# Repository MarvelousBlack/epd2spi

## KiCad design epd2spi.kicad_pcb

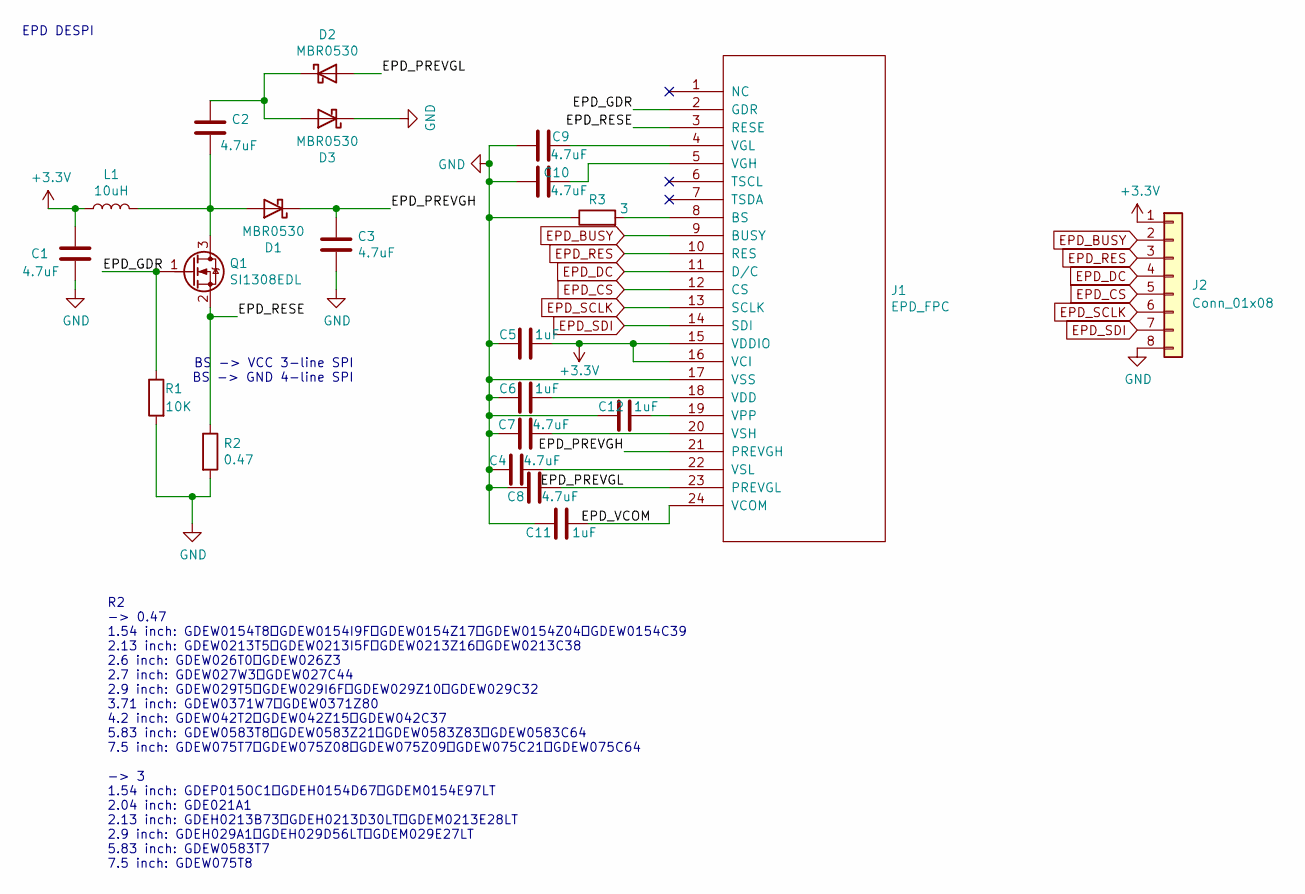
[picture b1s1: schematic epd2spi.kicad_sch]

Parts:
C1, C2, C3, C4, C7, C8, C9, C10: 4.7uF; C_0603_1608Metric
C5, C6, C11, C12: 1uF; C_0603_1608Metric
D1, D2, D3: MBR0530; D_SOD-123
J1: EPD_FPC; FPC-SMD_24P-L17.5-W5.4-P0.50; LCSC C11092
J2: Conn_01x08; PinHeader_1x08_P2.54mm_Vertical
L1: 10uH; L_Taiyo-Yuden_MD-4040
Q1: SI1308EDL; SOT-323_SC-70
R1: 10K; R_0603_1608Metric
R2: 0.47; R_0805_2012Metric
R3: 3; R_0805_2012Metric

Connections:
+3V3: C1.1, C5.1, J1.15 (VDDIO), J1.16 (VCI), J2.1, L1.1
/EPD_GDR: J1.2 (GDR), Q1.1 (G), R1.1
/EPD_PREVGH: C3.1, D1.1 (K), J1.21 (PREVGH)
/EPD_PREVGL: C8.2, D2.2 (A), J1.23 (PREVGL)
/EPD_RESE: J1.3 (RESE), Q1.2 (S), R2.1
/EPD_VCOM: C11.2, J1.24 (VCOM)
EPD_BUSY: J1.9 (BUSY), J2.2
EPD_CS: J1.12 (CS), J2.5
EPD_DC: J1.11 (D/C), J2.4
EPD_RES: J1.10 (RES), J2.3
EPD_SCLK: J1.13 (SCLK), J2.6
EPD_SDI: J1.14 (SDI), J2.7
GND: C1.2, C3.2, C4.1, C5.2, C6.2, C7.1, C8.1, C9.1, C10.1, C11.1, C12.2, D3.1 (K), J1.17 (VSS), J2.8, R1.2, R2.2, R3.1
unnamed: C2.1, D2.1 (K), D3.2 (A)
unnamed: C2.2, D1.2 (A), L1.2, Q1.3 (D)
unnamed: C4.2, J1.22 (VSL)
unnamed: C6.1, J1.18 (VDD)
unnamed: C7.2, J1.20 (VSH)
unnamed: C9.2, J1.4 (VGL)
unnamed: C10.2, J1.5 (VGH)
unnamed: C12.1, J1.19 (VPP)
unnamed: J1.8 (BS), R3.2
no_connect_23: J1.1 (NC)
no_connect_24: J1.6 (TSCL)
no_connect_25: J1.7 (TSDA)

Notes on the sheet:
EPD DESPI
R2 -> 0.47 1.54 inch: GDEW0154T8、GDEW0154I9F、GDEW0154Z17、GDEW0154Z04、GDEW0154C39 2.13 inch: GDEW0213T5、GDEW0213I5F、GDEW0213Z16、GDEW0213C38 2.6 inch: GDEW026T0、GDEW026Z3 2.7 inch: GDEW027W3、GDEW027C44 2.9 inch: GDEW029T5、GDEW029I6F、GDEW029Z10、GDEW029C32 3.71 inch: GDEW0371W7、GDEW0371Z80 4.2 inch: GD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
BS -> VCC 3-line SPI BS -> GND 4-line SPI

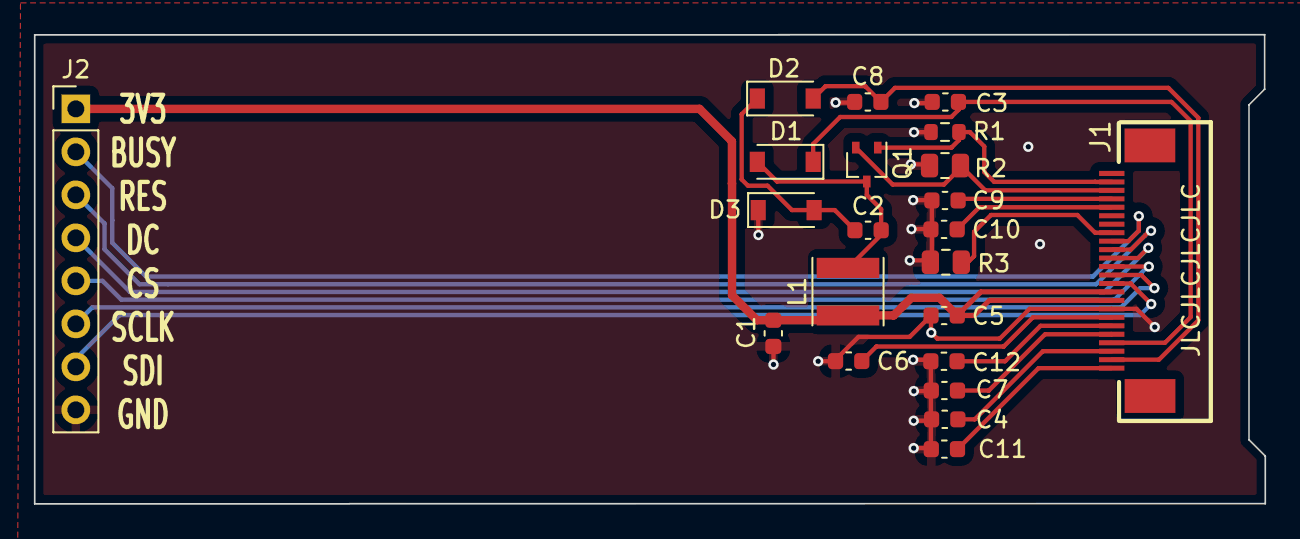
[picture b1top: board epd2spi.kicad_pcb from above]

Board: 2 copper layers, 72.7 x 27.7 mm, 22 parts (0 on the bottom side), 22 nets.

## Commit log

2021-01-12 epd2spi
2021-01-17 Change the size and re-route
2021-01-17 change J1 connector 25 26 pin to no net
